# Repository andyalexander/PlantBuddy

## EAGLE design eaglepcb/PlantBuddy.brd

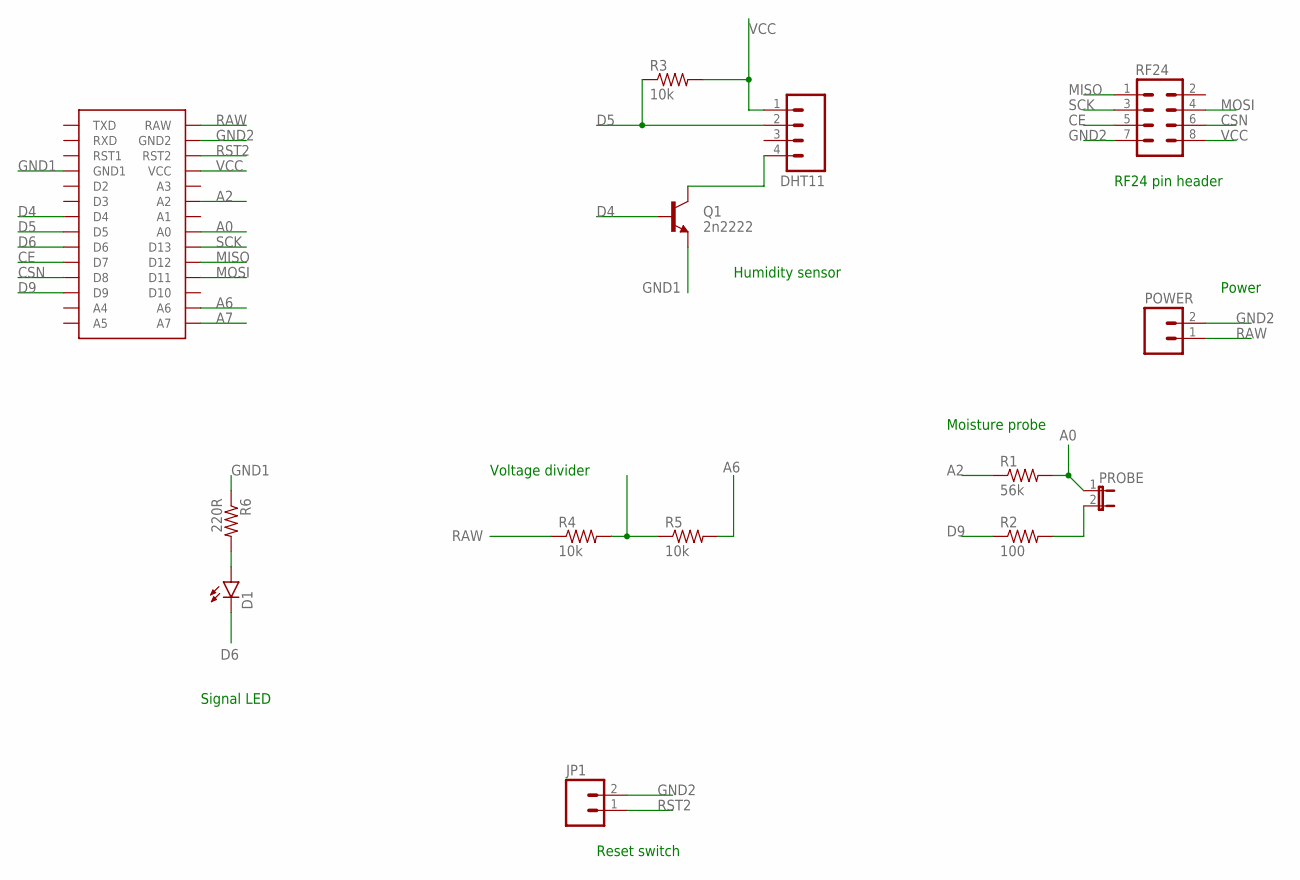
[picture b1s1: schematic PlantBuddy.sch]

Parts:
D1: LED5MM
DHT11: M04PTH; 1X04
JP1: M021X02_NO_SILK; 1X02_NO_SILK
POWER: M021X02_NO_SILK; 1X02_NO_SILK
PROBE: JUMPER-2PTH; 1X02
Q1: 2n2222; TO-92-AMMO
R1: 56k; AXIAL-0.3-KIT
R2: 100; AXIAL-0.3-KIT
R3, R4, R5: 10k; AXIAL-0.3-KIT
R6: 220R; AXIAL-0.3-KIT
RF24: M04X2; 2X4
U$1: PRO-MINIPRO-MINI-328P_1; PRO-MINI

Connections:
A0: PROBE.1, R1.P$2 (2), U$1.P$20 (A0)
A2: R1.P$1 (1), U$1.P$18 (A2)
A6: R5.P$2 (2), U$1.P$39 (A6)
A7: R4.P$2 (2), R5.P$1 (1), U$1.P$40 (A7)
CE: RF24.5, U$1.P$10 (D7)
CSN: RF24.6, U$1.P$11 (D8)
D4: Q1.2 (B), U$1.P$7 (D4)
D5: DHT11.2, R3.P$1 (1), U$1.P$8 (D5)
D6: D1.K (C), U$1.P$9 (D6)
D9: R2.P$1 (1), U$1.P$12 (D9)
GND1: Q1.3 (E), R6.P$1 (1), U$1.P$4 (GND1)
GND2: JP1.2, POWER.2, RF24.7, U$1.P$14 (GND2)
MISO: RF24.1, U$1.P$22 (D12)
MOSI: RF24.4, U$1.P$23 (D11)
unnamed: PROBE.2, R2.P$2 (2)
unnamed: DHT11.4, Q1.1 (C)
unnamed: D1.A, R6.P$2 (2)
RAW: POWER.1, R4.P$1 (1), U$1.P$13 (RAW)
RST2: JP1.1, U$1.P$15 (RST2)
SCK: RF24.3, U$1.P$21 (D13)
VCC: DHT11.1, R3.P$2 (2), RF24.8, U$1.P$16 (VCC)

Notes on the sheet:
Voltage divider
Humidity sensor
Reset switch
Power
Moisture probe
Signal LED
RF24 pin header

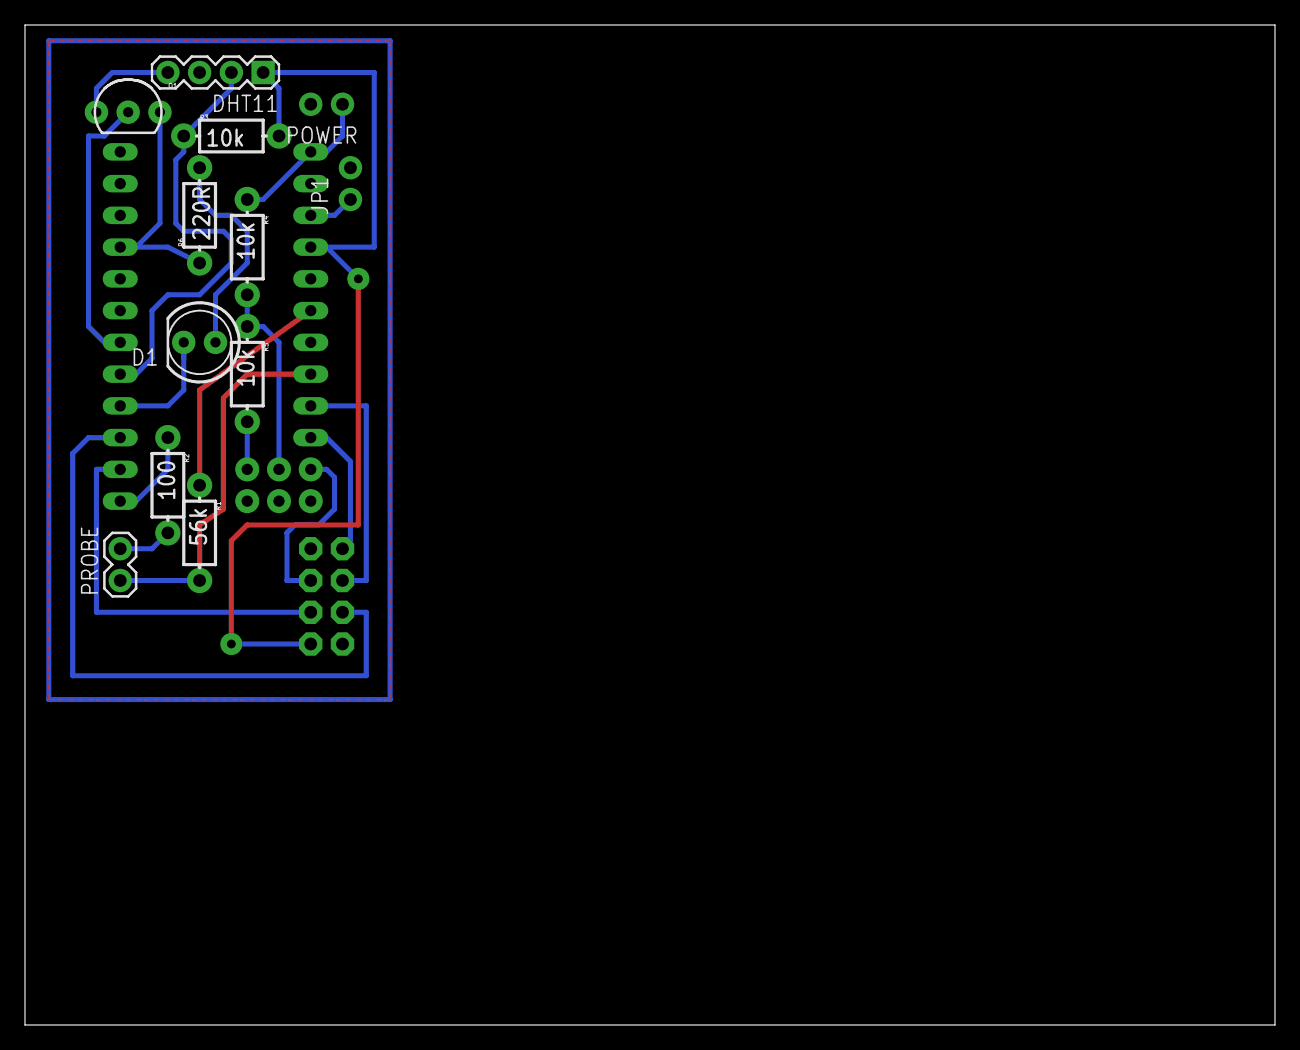
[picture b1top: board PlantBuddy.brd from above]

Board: 2 copper layers, 100.0 x 80.0 mm, 14 parts (1 on the bottom side), 21 nets.

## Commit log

2015-04-16 Iniital commit
2015-04-16 Add README

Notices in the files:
parts and their libraries:
SparkFun-LED: Licensing: Creative Commons ShareAlike 4.0 International - https://creativecommons.org/licenses/by-sa/4.0
